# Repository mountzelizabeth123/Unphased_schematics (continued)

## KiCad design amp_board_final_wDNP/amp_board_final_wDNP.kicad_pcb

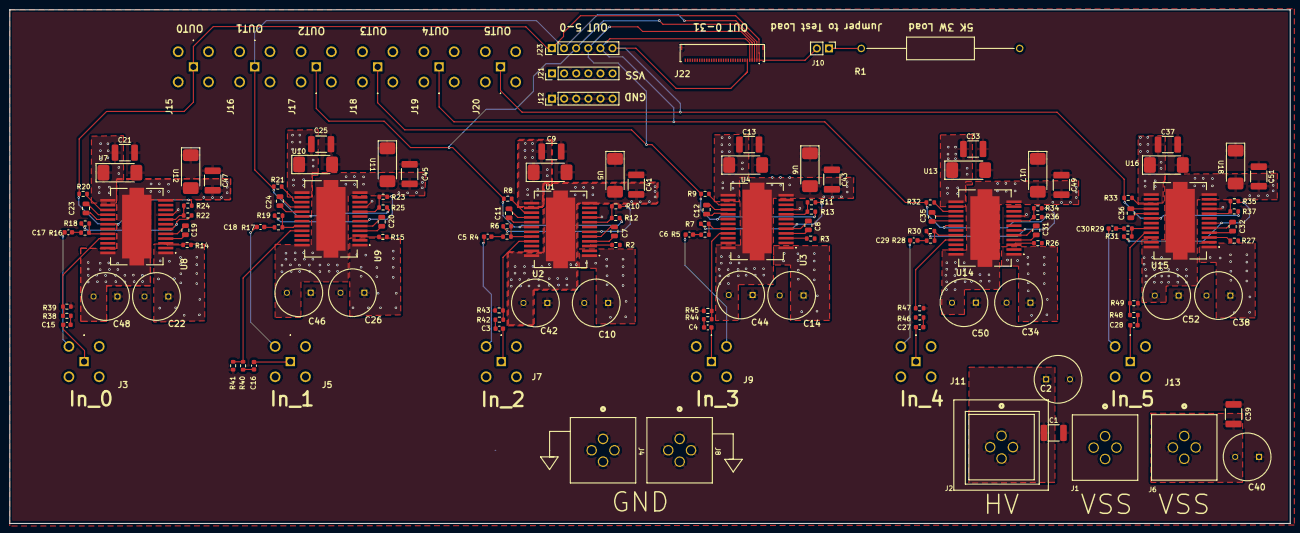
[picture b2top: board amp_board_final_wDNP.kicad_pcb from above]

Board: 4 copper layers, 268.3 x 107.7 mm, 141 parts (0 on the bottom side), 94 nets.

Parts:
C1, C9, C13, C21, C25, C33, C37, C39, C41, C43, C45, C47, C49, C51: 0.1u, 500V; C_1812_4532Metric
C2, C10, C14, C22, C26, C34, C38, C40, C42, C44, C46, C48, C50, C52: EEU-EB2G100
C3, C4, C5, C6, C15, C16, C17, C18, C27, C28, C29, C30: 0.1u, 10V; C_0603_1608Metric
C7, C8, C19, C20, C31, C32: 0.75pF, 250V; C_0805_2012Metric
C11, C12, C23, C24, C35, C36: 0.2pF, 250V; C_0805_2012Metric
J1, J4, J6, J8: CT3151V1-0; banana_plug_CT3151V1-0
J2: CT3151V1-2; banana_plug_CT3151V1-0
J3, J5, J7, J9, J11, J13, J15, J16, J17, J18, J19, J20: SMA_RF2-04A-T-00-50-G; 112404
J10: Conn_01x02_Pin; PinHeader_1x02_P2.54mm_Vertical
J12, J21, J23: Conn_01x06_Pin; PinHeader_1x06_P2.54mm_Vertical
J22: 503480-3200; Molex_5034803200
R1: 5k, 3W; RESAD3322W86L1422D475
R2, R3, R8, R9, R14, R15, R20, R21, R26, R27, R32, R33: 22.6; R_0603_1608Metric
R4, R5, R10, R11, R16, R17, R22, R23, R28, R29, R34, R35, R38, R40, R42, R44, R46, R48: 10; R_0603_1608Metric
R6, R7, R12, R13, R18, R19, R24, R25, R30, R31, R36, R37: 70.7; R_0603_1608Metric
R39, R41, R43, R45, R47, R49: 100; R_0603_1608Metric
U1, U4, U5, U6, U7, U10, U11, U12, U13, U16, U17, U18: SMCJ150A; SMCJ150A-13-F
U2, U3, U8, U9, U14, U15: PA343; PA341DF

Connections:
/amp_0/input_0a_lv: R38.1, R39.2, U8.21 (+IN_A)
/amp_0/input_0b_lv: C17.2, R16.2
/amp_0/input_1a_lv: R40.1, R41.2, U9.21 (+IN_A)
/amp_0/input_1b_lv: C18.2, R17.2
/amp_0/output0_mv: R18.1, R22.2, U8.6 (OUT_A)
/amp_0/output1_mv: R19.1, R23.2, U9.6 (OUT_A)
/amp_1/input_2a_lv: R42.1, R43.2, U2.21 (+IN_A)
/amp_1/input_2b_lv: C5.2, R4.2
/amp_1/input_3a_lv: R44.1, R45.2, U3.21 (+IN_A)
/amp_1/input_3b_lv: C6.2, R5.2
/amp_1/output2_mv: R6.1, R10.2, U2.6 (OUT_A)
/amp_1/output3_mv: R7.1, R11.2, U3.6 (OUT_A)
/amp_2/input_4a_lv: R46.1, R47.2, U14.21 (+IN_A)
/amp_2/input_4b_lv: C29.2, R28.2
/amp_2/input_5a_lv: R48.1, R49.2, U15.21 (+IN_A)
/amp_2/input_5b_lv: C30.2, R29.2
/amp_2/output4_mv: R30.1, R34.2, U14.6 (OUT_A)
/amp_2/output5_mv: R31.1, R35.2, U15.6 (OUT_A)
GND: C1.2, C2.2 (-), C9.2, C10.2 (-), C13.2, C14.2 (-), C21.2, C22.2 (-), C25.2, C26.2 (-), C33.2, C34.2 (-), C37.2, C38.2 (-), C39.2, C40.1 (+), C41.1, C42.1 (+), C43.1, C44.1 (+), C45.1, C46.1 (+), C47.1, C48.1 (+), C49.1, C50.1 (+), C51.1, C52.1 (+), J4.1, J4.2, J4.3, J4.4, J8.1, J8.2, J8.3, J8.4, J12.1, J12.2, J12.3, J12.4, J12.5, J12.6, J22.33, J22.34, R39.1, R41.1, R43.1, R45.1, R47.1, R49.1, U1.2 (A), U2.9 (+IN_B), U3.9 (+IN_B), U4.2 (A), U5.1 (K), U6.1 (K), U7.2 (A), U8.9 (+IN_B), U9.9 (+IN_B), U10.2 (A), U11.1 (K), U12.1 (K), U13.2 (A), U14.9 (+IN_B), U15.9 (+IN_B), U16.2 (A), U17.1 (K), U18.1 (K)
HV: C1.1, C2.1 (+), C9.1, C10.1 (+), C13.1, C14.1 (+), C21.1, C22.1 (+), C25.1, C26.1 (+), C33.1, C34.1 (+), C37.1, C38.1 (+), J2.1, J2.2, J2.3, J2.4, U1.1 (K), U2.1, U2.13, U3.1, U3.13, U4.1 (K), U7.1 (K), U8.1, U8.13, U9.1, U9.13, U10.1 (K), U13.1 (K), U14.1, U14.13, U15.1, U15.13, U16.1 (K)
unnamed: C3.2, R42.2
unnamed: C4.2, R44.2
unnamed: C15.2, R38.2
unnamed: C16.2, R40.2
unnamed: C27.2, R46.2
unnamed: C28.2, R48.2
unnamed: J10.1, R1.1
unnamed: R4.1, R6.2, U2.20 (-IN_A)
unnamed: C7.1, U2.4 (CC_A_1)
unnamed: C7.2, U2.5 (CC_A_2)
unnamed: R2.1, U2.3 (CL_A)
unnamed: R10.1, R12.2, U2.8 (-IN_B)
unnamed: C11.1, U2.16 (CC_B_1)
unnamed: C11.2, U2.17 (CC_B_2)
unnamed: R8.1, U2.15 (CL_B)
unnamed: R5.1, R7.2, U3.20 (-IN_A)
unnamed: C8.1, U3.4 (CC_A_1)
unnamed: C8.2, U3.5 (CC_A_2)
unnamed: R3.1, U3.3 (CL_A)
unnamed: R11.1, R13.2, U3.8 (-IN_B)
unnamed: C12.1, U3.16 (CC_B_1)
unnamed: C12.2, U3.17 (CC_B_2)
unnamed: R9.1, U3.15 (CL_B)
unnamed: R16.1, R18.2, U8.20 (-IN_A)
unnamed: C19.1, U8.4 (CC_A_1)
unnamed: C19.2, U8.5 (CC_A_2)
unnamed: R14.1, U8.3 (CL_A)
unnamed: R22.1, R24.2, U8.8 (-IN_B)
unnamed: C23.1, U8.16 (CC_B_1)
unnamed: C23.2, U8.17 (CC_B_2)
unnamed: R20.1, U8.15 (CL_B)
unnamed: R17.1, R19.2, U9.20 (-IN_A)
unnamed: C20.1, U9.4 (CC_A_1)
unnamed: C20.2, U9.5 (CC_A_2)
unnamed: R15.1, U9.3 (CL_A)
unnamed: R23.1, R25.2, U9.8 (-IN_B)
unnamed: C24.1, U9.16 (CC_B_1)
unnamed: C24.2, U9.17 (CC_B_2)
unnamed: R21.1, U9.15 (CL_B)
unnamed: R28.1, R30.2, U14.20 (-IN_A)
unnamed: C31.1, U14.4 (CC_A_1)
unnamed: C31.2, U14.5 (CC_A_2)
unnamed: R26.1, U14.3 (CL_A)
unnamed: R34.1, R36.2, U14.8 (-IN_B)
unnamed: C35.1, U14.16 (CC_B_1)
unnamed: C35.2, U14.17 (CC_B_2)
unnamed: R32.1, U14.15 (CL_B)
unnamed: R29.1, R31.2, U15.20 (-IN_A)
unnamed: C32.1, U15.4 (CC_A_1)
unnamed: C32.2, U15.5 (CC_A_2)
unnamed: R27.1, U15.3 (CL_A)
unnamed: R35.1, R37.2, U15.8 (-IN_B)
unnamed: C36.1, U15.16 (CC_B_1)
unnamed: C36.2, U15.17 (CC_B_2)
unnamed: R33.1, U15.15 (CL_B)
VSS: C39.1, C40.2 (-), C41.2, C42.2 (-), C43.2, C44.2 (-), C45.2, C46.2 (-), C47.2, C48.2 (-), C49.2, C50.2 (-), C51.2, C52.2 (-), J1.1, J1.2, J1.3, J1.4, J6.1, J6.2, J6.3, J6.4, J15.2, J15.3 (Ext), J15.4 (Ext), J15.5 (Ext), J16.2, J16.3 (Ext), J16.4 (Ext), J16.5 (Ext), J17.2, J17.3 (Ext), J17.4 (Ext), J17.5 (Ext), J18.2, J18.3 (Ext), J18.4 (Ext), J18.5 (Ext), J19.2, J19.3 (Ext), J19.4 (Ext), J19.5 (Ext), J20.2, J20.3 (Ext), J20.4 (Ext), J20.5 (Ext), J21.1, J21.2, J21.3, J21.4, J21.5, J21.6, R1.2, U2.12, U2.24, U2.25 (EPAD), U2.26, U2.27, U3.12, U3.24, U3.25 (EPAD), U3.26, U3.27, U5.2 (A), U6.2 (A), U8.12, U8.24, U8.25 (EPAD), U8.26, U8.27, U9.12, U9.24, U9.25 (EPAD), U9.26, U9.27, U11.2 (A), U12.2 (A), U14.12, U14.24, U14.25 (EPAD), U14.26, U14.27, U15.12, U15.24, U15.25 (EPAD), U15.26, U15.27, U17.2 (A), U18.2 (A)
input_0a: C15.1, J3.1
input_0b: C17.1, J3.2, J3.3 (Ext), J3.4 (Ext), J3.5 (Ext)
input_1a: C16.1, J5.1
input_1b: C18.1, J5.2, J5.3 (Ext), J5.4 (Ext), J5.5 (Ext)
input_2a: C3.1, J7.1
input_2b: C5.1, J7.2, J7.3 (Ext), J7.4 (Ext), J7.5 (Ext)
input_3a: C4.1, J9.1
input_3b: C6.1, J9.2, J9.3 (Ext), J9.4 (Ext), J9.5 (Ext)
input_4a: C27.1, J11.1
input_4b: C29.1, J11.2, J11.3 (Ext), J11.4 (Ext), J11.5 (Ext)
input_5a: C28.1, J13.1
input_5b: C30.1, J13.2, J13.3 (Ext), J13.4 (Ext), J13.5 (Ext)
output_0: J10.2, J15.1, J22.1, J23.1, R20.2, R24.1, U8.18 (OUT_B)
output_1: J16.1, J22.2, J23.2, R21.2, R25.1, U9.18 (OUT_B)
output_2: J17.1, J22.3, J23.3, R8.2, R12.1, U2.18 (OUT_B)
output_3: J18.1, J22.4, J23.4, R9.2, R13.1, U3.18 (OUT_B)
output_4: J19.1, J22.5, J23.5, R32.2, R36.1, U14.18 (OUT_B)
output_5: J20.1, J22.6, J23.6, R33.2, R37.1, U15.18 (OUT_B)

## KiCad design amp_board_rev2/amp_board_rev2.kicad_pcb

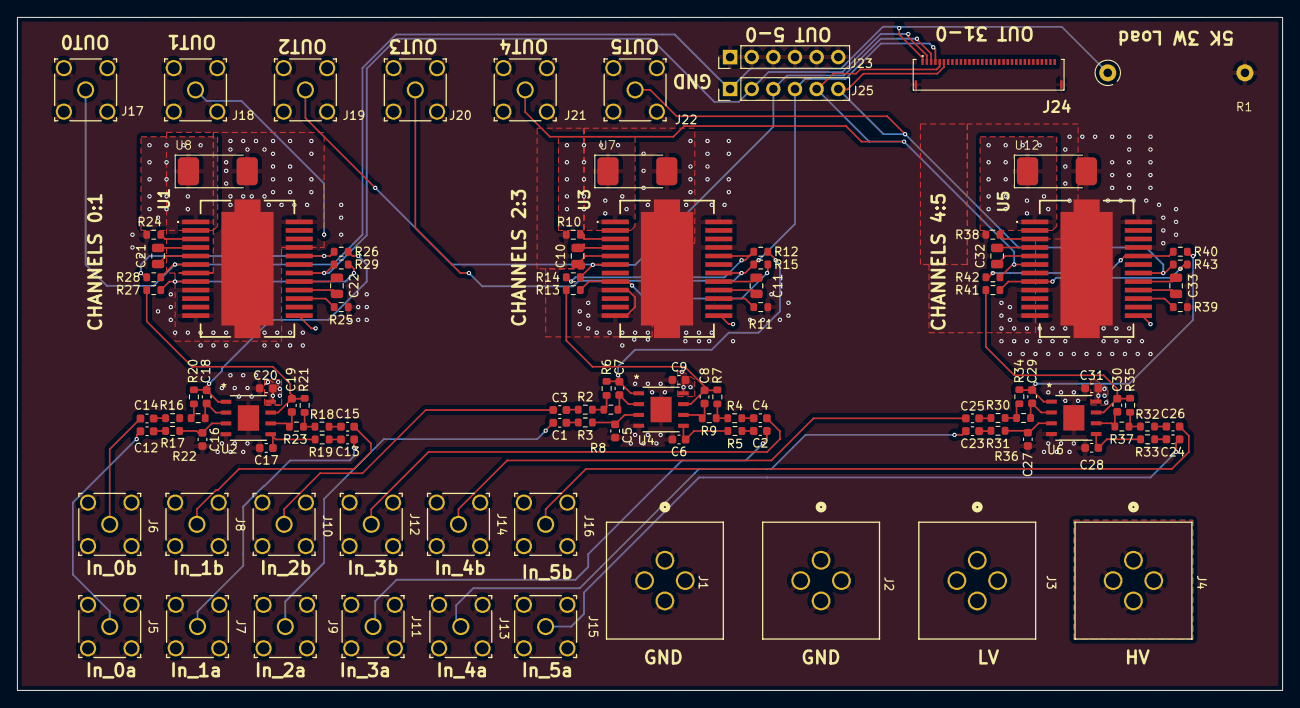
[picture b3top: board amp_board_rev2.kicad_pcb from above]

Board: 4 copper layers, 148.5 x 79.0 mm, 110 parts (0 on the bottom side), 84 nets.

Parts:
C1, C2, C3, C4, C9, C12, C13, C14, C15, C20, C23, C24, C25, C26, C31: 0.1u; C_0603_1608Metric
C5, C6, C16, C17, C27, C28: 1.56pF; C_0603_1608Metric
C7, C8, C18, C19, C29, C30: 1pF; C_0603_1608Metric
C10, C11, C21, C22, C32, C33: 0.75pF, 500V; C_0805_2012Metric
J1, J2: CT3151V1-0; banana_plug_CT3151V1-0
J3, J4: CT3151V1-2; banana_plug_CT3151V1-0
J5, J6, J7, J8, J9, J10, J11, J12, J13, J14, J15, J16, J17, J18, J19, J20, J21, J22: SMA_RF2-04A-T-00-50-G; CONN_RF2-04A-T-00-50-G_ADM
J23, J25: Conn_01x06_Pin; PinHeader_1x06_P2.54mm_Vertical
J24: 503480-3200; Molex_5034803200
R1: R_US; RS02B5K000FB12
R2, R4, R16, R18, R30, R32: 1k; R_0603_1608Metric
R3, R5, R8, R9, R17, R19, R22, R23, R31, R33, R36, R37: R_US; R_0603_1608Metric
R6, R7, R20, R21, R34, R35: 4k; R_0603_1608Metric
R10, R11, R24, R25, R38, R39: 22.6; R_0603_1608Metric
R12, R13, R26, R27, R40, R41: 1R; R_0603_1608Metric
R14, R15, R28, R29, R42, R43: 25R; R_0603_1608Metric
U1, U3, U5: PA341DF
U2, U4, U6: OPA2211AIDDAR_L
U7, U8, U12: SMCJ150A-13-F

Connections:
+12V: C9.1, C20.1, C31.1, J3.1, J3.2, J3.3, J3.4, U2.8, U4.8, U6.8
/amp_0/output0_lv: C18.1, R20.1, R26.2, U2.1 (OUTA)
/amp_0/output1_lv: C19.1, R21.1, R27.2, U2.7 (OUTB)
/amp_1/output2_lv: C7.1, R6.1, R12.2, U4.1 (OUTA)
/amp_1/output3_lv: C8.1, R7.1, R13.2, U4.7 (OUTB)
/amp_2/output4_lv: C29.1, R34.1, R40.2, U6.1 (OUTA)
/amp_2/output5_lv: C30.1, R35.1, R41.2, U6.7 (OUTB)
GND: C5.2, C6.2, C9.2, C16.2, C17.2, C20.2, C27.2, C28.2, C31.2, J1.1, J1.2, J1.3, J1.4, J2.1, J2.2, J2.3, J2.4, J5.2, J5.3 (Ext), J5.4 (Ext), J5.5 (Ext), J6.2, J6.3 (Ext), J6.4 (Ext), J6.5 (Ext), J7.2, J7.3 (Ext), J7.4 (Ext), J7.5 (Ext), J8.2, J8.3 (Ext), J8.4 (Ext), J8.5 (Ext), J9.2, J9.3 (Ext), J9.4 (Ext), J9.5 (Ext), J10.2, J10.3 (Ext), J10.4 (Ext), J10.5 (Ext), J11.2, J11.3 (Ext), J11.4 (Ext), J11.5 (Ext), J12.2, J12.3 (Ext), J12.4 (Ext), J12.5 (Ext), J13.2, J13.3 (Ext), J13.4 (Ext), J13.5 (Ext), J14.2, J14.3 (Ext), J14.4 (Ext), J14.5 (Ext), J15.2, J15.3 (Ext), J15.4 (Ext), J15.5 (Ext), J16.2, J16.3 (Ext), J16.4 (Ext), J16.5 (Ext), J17.2, J17.3 (Ext), J17.4 (Ext), J17.5 (Ext), J18.2, J18.3 (Ext), J18.4 (Ext), J18.5 (Ext), J19.2, J19.3 (Ext), J19.4 (Ext), J19.5 (Ext), J20.2, J20.3 (Ext), J20.4 (Ext), J20.5 (Ext), J21.2, J21.3 (Ext), J21.4 (Ext), J21.5 (Ext), J22.2, J22.3 (Ext), J22.4 (Ext), J22.5 (Ext), J23.1, J23.2, J23.3, J23.4, J23.5, J23.6, J24.33, J24.34, R1.2, R10.2, R11.2, R24.2, R25.2, R38.2, R39.2, U1.9 (+IN_B), U1.12, U1.21 (+IN_A), U1.24, U1.25 (EPAD), U1.26, U1.27, U2.4, U2.EPAD, U3.9 (+IN_B), U3.12, U3.21 (+IN_A), U3.24, U3.25 (EPAD), U3.26, U3.27, U4.4, U4.EPAD, U5.9 (+IN_B), U5.12, U5.21 (+IN_A), U5.24, U5.25 (EPAD), U5.26, U5.27, U6.4, U6.EPAD, U7.2 (A), U8.2 (A), U12.2 (A)
HV: J4.1, J4.2, J4.3, J4.4, U1.1, U1.13, U3.1, U3.13, U5.1, U5.13, U7.1 (K), U8.1 (K), U12.1 (K)
unnamed: C1.2, R3.2
unnamed: C2.2, R5.2
unnamed: C3.2, R2.2
unnamed: C4.2, R4.2
unnamed: C12.2, R17.2
unnamed: C13.2, R19.2
unnamed: C14.2, R16.2
unnamed: C15.2, R18.2
unnamed: C23.2, R31.2
unnamed: C24.2, R33.2
unnamed: C25.2, R30.2
unnamed: C26.2, R32.2
unnamed: R2.1, R6.2, R8.2
unnamed: R4.1, R7.2, R9.2
unnamed: R16.1, R20.2, R22.2
unnamed: R18.1, R21.2, R23.2
unnamed: R30.1, R34.2, R36.2
unnamed: R32.1, R35.2, R37.2
unnamed: R26.1, R28.2, U1.20 (-IN_A)
unnamed: C21.1, U1.4 (CC_A_1)
unnamed: C21.2, U1.5 (CC_A_2)
unnamed: R24.1, U1.3 (CL_A)
unnamed: U1.2 (NC_1), U1.7 (NC_2), U1.10 (NC_3), U1.11 (NC_4), U1.14 (NC_5), U1.19 (NC_6), U1.22 (NC_7), U1.23 (NC_8)
unnamed: R27.1, R29.2, U1.8 (-IN_B)
unnamed: C22.1, U1.16 (CC_B_1)
unnamed: C22.2, U1.17 (CC_B_2)
unnamed: R25.1, U1.15 (CL_B)
unnamed: C16.1, R17.1, U2.3 (INA+)
unnamed: C18.2, R22.1, U2.2 (INA-)
unnamed: C17.1, R19.1, U2.5 (INB+)
unnamed: C19.2, R23.1, U2.6 (INB-)
unnamed: R12.1, R14.2, U3.20 (-IN_A)
unnamed: C10.1, U3.4 (CC_A_1)
unnamed: C10.2, U3.5 (CC_A_2)
unnamed: R10.1, U3.3 (CL_A)
unnamed: U3.2 (NC_1), U3.7 (NC_2), U3.10 (NC_3), U3.11 (NC_4), U3.14 (NC_5), U3.19 (NC_6), U3.22 (NC_7), U3.23 (NC_8)
unnamed: R13.1, R15.2, U3.8 (-IN_B)
unnamed: C11.1, U3.16 (CC_B_1)
unnamed: C11.2, U3.17 (CC_B_2)
unnamed: R11.1, U3.15 (CL_B)
unnamed: C5.1, R3.1, U4.3 (INA+)
unnamed: C7.2, R8.1, U4.2 (INA-)
unnamed: C6.1, R5.1, U4.5 (INB+)
unnamed: C8.2, R9.1, U4.6 (INB-)
unnamed: R40.1, R42.2, U5.20 (-IN_A)
unnamed: C32.1, U5.4 (CC_A_1)
unnamed: C32.2, U5.5 (CC_A_2)
unnamed: R38.1, U5.3 (CL_A)
unnamed: U5.2 (NC_1), U5.7 (NC_2), U5.10 (NC_3), U5.11 (NC_4), U5.14 (NC_5), U5.19 (NC_6), U5.22 (NC_7), U5.23 (NC_8)
unnamed: R41.1, R43.2, U5.8 (-IN_B)
unnamed: C33.1, U5.16 (CC_B_1)
unnamed: C33.2, U5.17 (CC_B_2)
unnamed: R39.1, U5.15 (CL_B)
unnamed: C27.1, R31.1, U6.3 (INA+)
unnamed: C29.2, R36.1, U6.2 (INA-)
unnamed: C28.1, R33.1, U6.5 (INB+)
unnamed: C30.2, R37.1, U6.6 (INB-)
input_0a: C12.1, J5.1
input_0b: C14.1, J6.1
input_1a: C13.1, J7.1
input_1b: C15.1, J8.1
input_2a: C1.1, J9.1
input_2b: C3.1, J10.1
input_3a: C2.1, J11.1
input_3b: C4.1, J12.1
input_4a: C23.1, J13.1
input_4b: C25.1, J14.1
input_5a: C24.1, J15.1
input_5b: C26.1, J16.1
output_0: J17.1, J24.1, J25.1, R1.1, R28.1, U1.6 (OUT_A)
output_1: J18.1, J24.2, J25.2, R29.1, U1.18 (OUT_B)
output_2: J19.1, J24.3, J25.3, R14.1, U3.6 (OUT_A)
output_3: J20.1, J24.4, J25.4, R15.1, U3.18 (OUT_B)
output_4: J21.1, J24.5, J25.5, R42.1, U5.6 (OUT_A)
output_5: J22.1, J24.6, J25.6, R43.1, U5.18 (OUT_B)

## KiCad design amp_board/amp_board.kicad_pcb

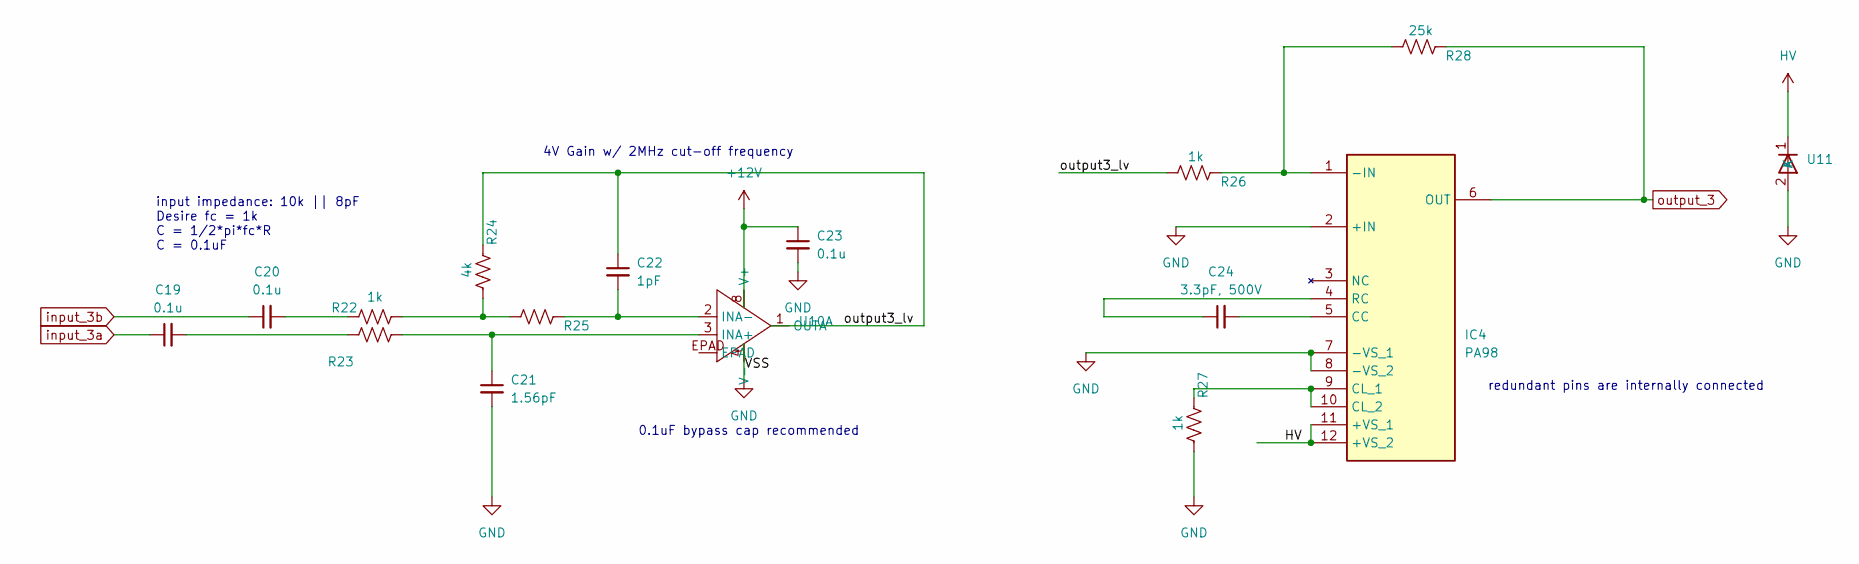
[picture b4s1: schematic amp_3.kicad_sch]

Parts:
C19, C20, C23: 0.1u; C_0603_1608Metric
C21: 1.56pF; C_0603_1608Metric
C22: 1pF; C_0603_1608Metric
C24: 3.3pF, 500V; C_0805_2012Metric
IC4: PA98; Mouser Part Number 137-PA98
R22, R26, R27: 1k; R_0603_1608Metric
R23, R25: R_US; R_0603_1608Metric
R24: 4k; R_0603_1608Metric
R28: 25k; R_0603_1608Metric
U10: OPA2211AIDDAR_L
U11: SMCJ150A-13-F

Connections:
+12V: C23.1, U10.8 (V+); also elsewhere on the board
/amp_3/output3_lv: C22.1, R24.1, R26.2, U10.1 (OUTA)
GND: C21.2, C23.2, IC4.2 (+IN), IC4.7 (-VS_1), IC4.8 (-VS_2), R27.2, U10.4 (V-), U11.2 (A); also elsewhere on the board
HV: IC4.11 (+VS_1), IC4.12 (+VS_2), U11.1 (K); also elsewhere on the board
unnamed: C19.2, R23.2
unnamed: C20.2, R22.2
unnamed: IC4.1 (-IN), R26.1, R28.2
unnamed: C24.2, IC4.5 (CC)
unnamed: IC4.9 (CL_1), IC4.10 (CL_2), R27.1
unnamed: C24.1, IC4.4 (RC)
unnamed: R22.1, R24.2, R25.2
unnamed: C21.1, R23.1, U10.3 (INA+)
unnamed: C22.2, R25.1, U10.2 (INA-)
input_3a: C19.1; also elsewhere on the board
input_3b: C20.1; also elsewhere on the board
output_3: IC4.6 (OUT), R28.1; also elsewhere on the board

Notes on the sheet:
input impedance: 10k || 8pF Desire fc = 1k C = 1/2*pi*fc*R C = 0.1uF
0.1uF bypass cap recommended
4V Gain w/ 2MHz cut-off frequency
redundant pins are internally connected

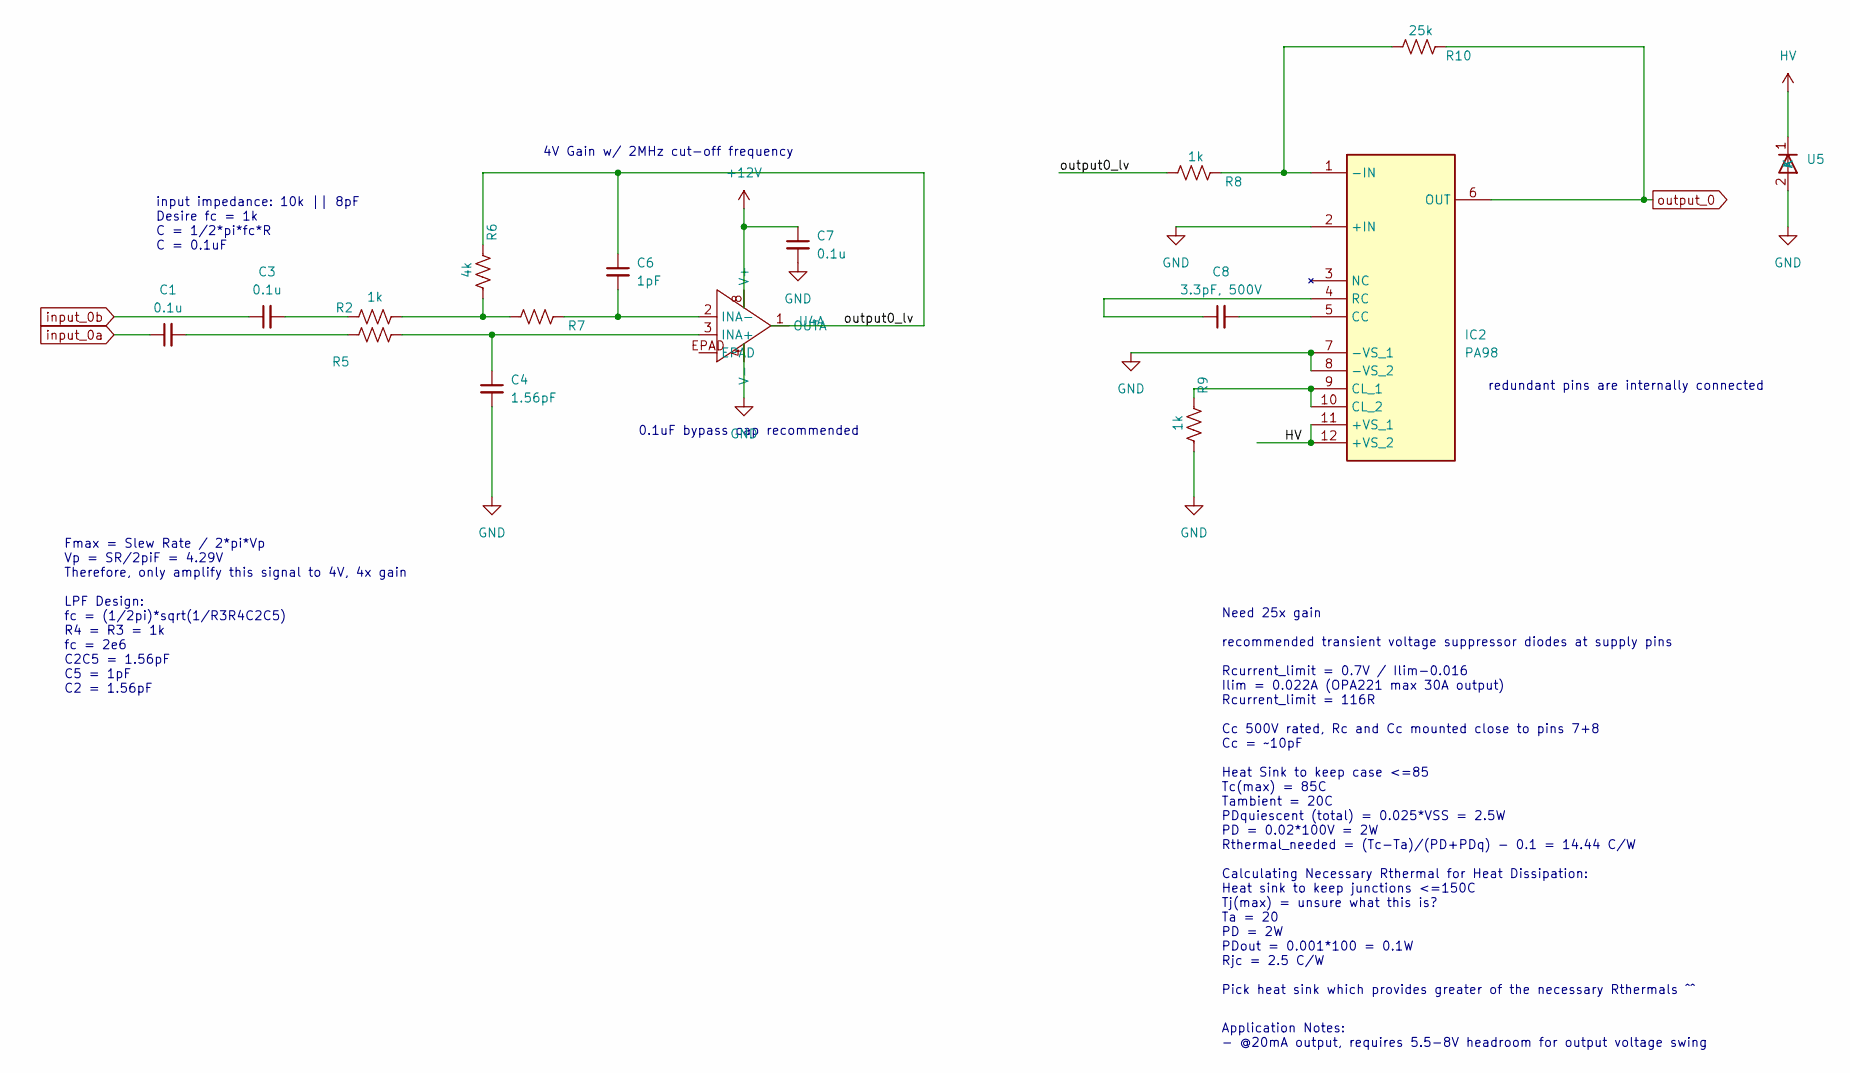
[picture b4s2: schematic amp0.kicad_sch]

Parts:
C1, C3, C7: 0.1u; C_0603_1608Metric
C4: 1.56pF; C_0603_1608Metric
C6: 1pF; C_0603_1608Metric
C8: 3.3pF, 500V; C_0805_2012Metric
IC2: PA98; Mouser Part Number 137-PA98
R2, R8, R9: 1k; R_0603_1608Metric
R5, R7: R_US; R_0603_1608Metric
R6: 4k; R_0603_1608Metric
R10: 25k; R_0603_1608Metric
U4: OPA2211AIDDAR_L
U5: SMCJ150A-13-F

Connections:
+12V: C7.1, U4.8 (V+); also elsewhere on the board
/amp_0/output0_lv: C6.1, R6.1, R8.2, U4.1 (OUTA)
GND: C4.2, C7.2, IC2.2 (+IN), IC2.7 (-VS_1), IC2.8 (-VS_2), R9.2, U4.4 (V-), U5.2 (A); also elsewhere on the board
HV: IC2.11 (+VS_1), IC2.12 (+VS_2), U5.1 (K); also elsewhere on the board
unnamed: C1.2, R5.2
unnamed: C3.2, R2.2
unnamed: IC2.1 (-IN), R8.1, R10.2
unnamed: C8.2, IC2.5 (CC)
unnamed: IC2.9 (CL_1), IC2.10 (CL_2), R9.1
unnamed: C8.1, IC2.4 (RC)
unnamed: R2.1, R6.2, R7.2
unnamed: C4.1, R5.1, U4.3 (INA+)
unnamed: C6.2, R7.1, U4.2 (INA-)
input_0a: C1.1; also elsewhere on the board
input_0b: C3.1; also elsewhere on the board
output_0: IC2.6 (OUT), R10.1; also elsewhere on the board

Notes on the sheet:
input impedance: 10k || 8pF Desire fc = 1k C = 1/2*pi*fc*R C = 0.1uF
redundant pins are internally connected
4V Gain w/ 2MHz cut-off frequency
Fmax = Slew Rate / 2*pi*Vp Vp = SR/2piF = 4.29V Therefore, only amplify this signal to 4V, 4x gain LPF Design: fc = (1/2pi)*sqrt(1/R3R4C2C5) R4 = R3 = 1k fc = 2e6 C2C5 = 1.56pF C5 = 1pF C2 = 1.56pF
0.1uF bypass cap recommended
Need 25x gain recommended transient voltage suppressor diodes at supply pins Rcurrent_limit = 0.7V / Ilim-0.016 Ilim = 0.022A (OPA221 max 30A output) Rcurrent_limit = 116R Cc 500V rated, Rc and Cc mounted close to pins 7+8 Cc = ~10pF Heat Sink to keep case <=85 Tc(max) = 85C Tambient = 20C PDquiesc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
Application Notes: - @20mA output, requires 5.5-8V headroom for output voltage swing

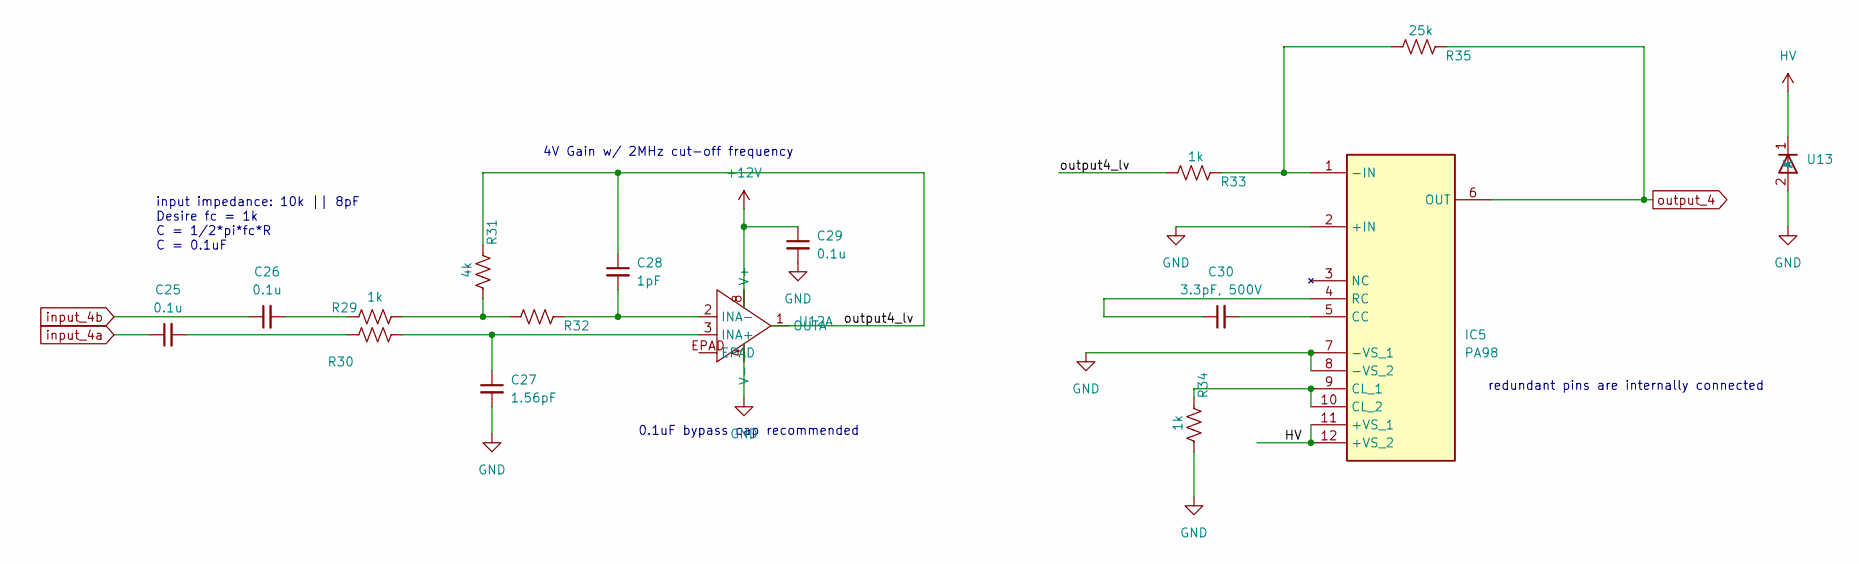
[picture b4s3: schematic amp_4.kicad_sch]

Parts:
C25, C26, C29: 0.1u; C_0603_1608Metric
C27: 1.56pF; C_0603_1608Metric
C28: 1pF; C_0603_1608Metric
C30: 3.3pF, 500V; C_0805_2012Metric
IC5: PA98; Mouser Part Number 137-PA98
R29, R33, R34: 1k; R_0603_1608Metric
R30, R32: R_US; R_0603_1608Metric
R31: 4k; R_0603_1608Metric
R35: 25k; R_0603_1608Metric
U12: OPA2211AIDDAR_L
U13: SMCJ150A-13-F

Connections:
+12V: C29.1, U12.8 (V+); also elsewhere on the board
/amp_4/output4_lv: C28.1, R31.1, R33.2, U12.1 (OUTA)
GND: C27.2, C29.2, IC5.2 (+IN), IC5.7 (-VS_1), IC5.8 (-VS_2), R34.2, U12.4 (V-), U13.2 (A); also elsewhere on the board
HV: IC5.11 (+VS_1), IC5.12 (+VS_2), U13.1 (K); also elsewhere on the board
unnamed: C25.2, R30.2
unnamed: C26.2, R29.2
unnamed: IC5.1 (-IN), R33.1, R35.2
unnamed: C30.2, IC5.5 (CC)
unnamed: IC5.9 (CL_1), IC5.10 (CL_2), R34.1
unnamed: C30.1, IC5.4 (RC)
unnamed: R29.1, R31.2, R32.2
unnamed: C27.1, R30.1, U12.3 (INA+)
unnamed: C28.2, R32.1, U12.2 (INA-)
input_4a: C25.1; also elsewhere on the board
input_4b: C26.1; also elsewhere on the board
output_4: IC5.6 (OUT), R35.1; also elsewhere on the board

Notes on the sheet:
redundant pins are internally connected
0.1uF bypass cap recommended
4V Gain w/ 2MHz cut-off frequency
input impedance: 10k || 8pF Desire fc = 1k C = 1/2*pi*fc*R C = 0.1uF

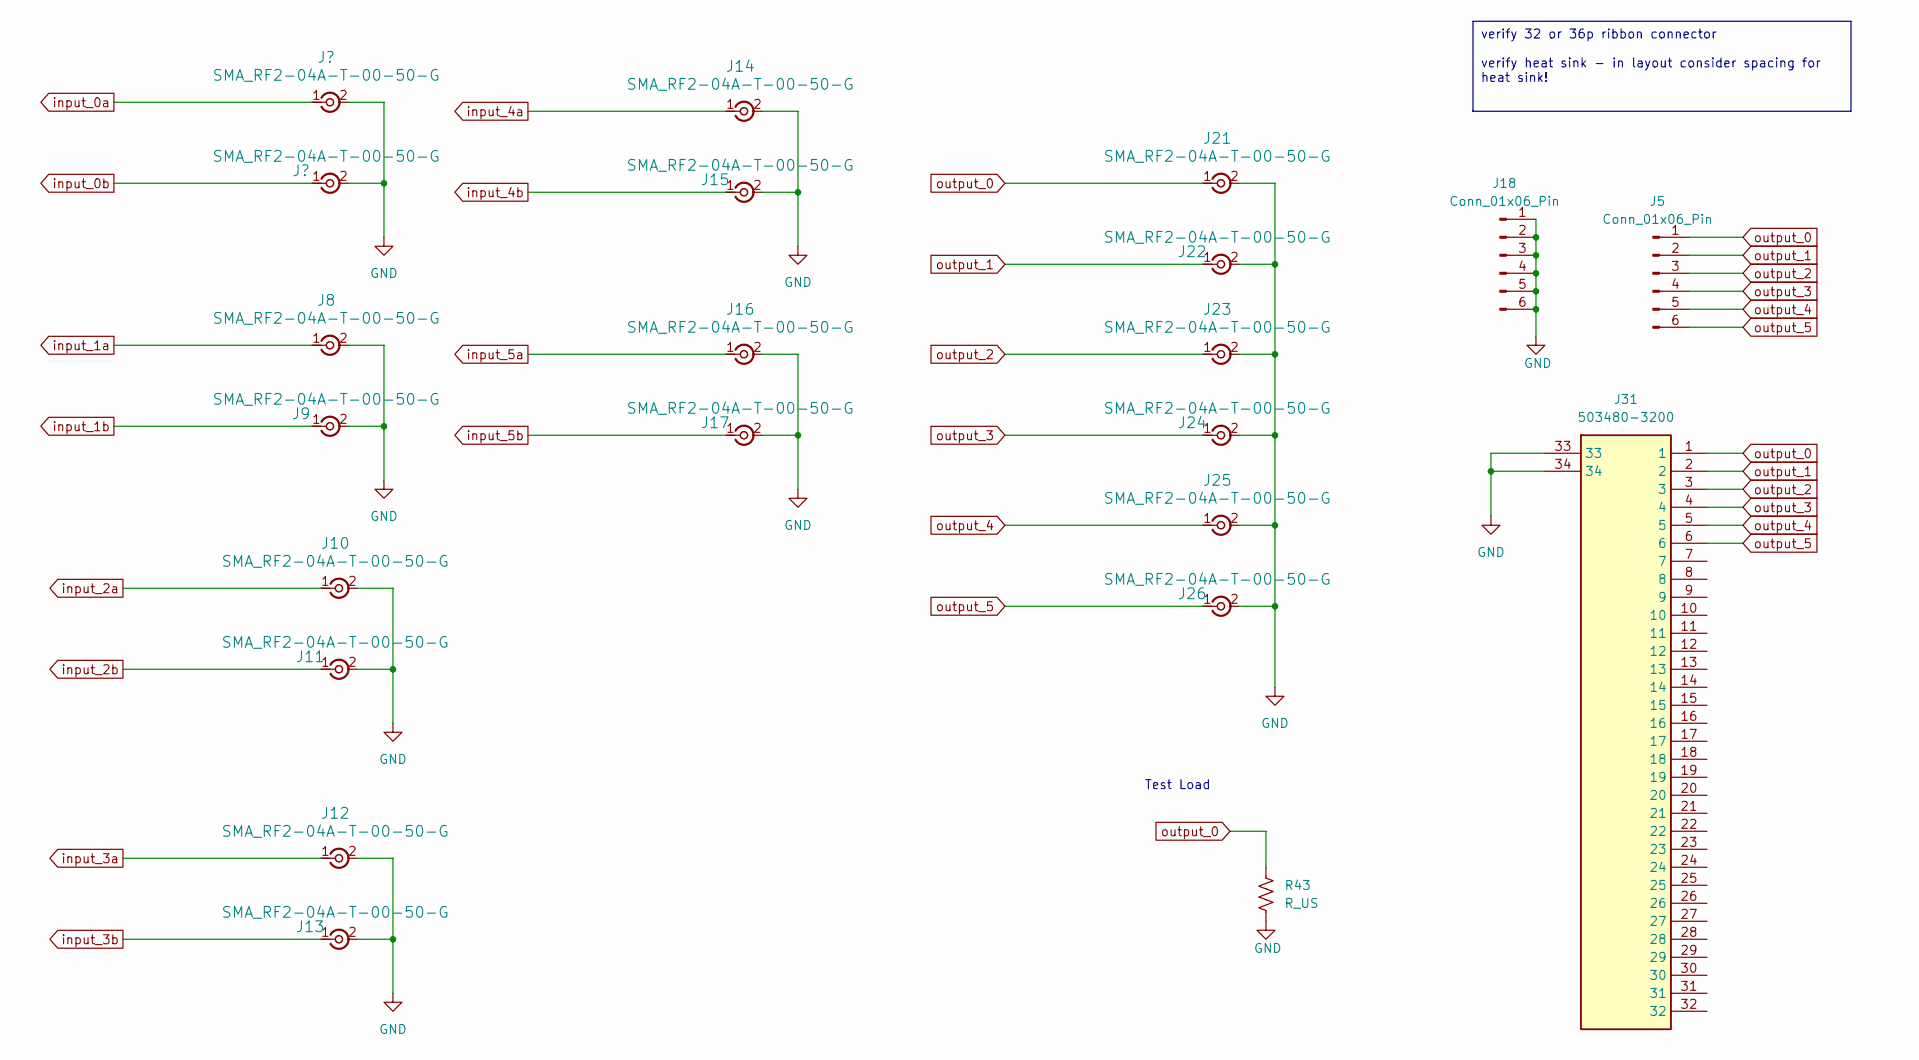
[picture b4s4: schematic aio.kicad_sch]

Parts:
J5, J18: Conn_01x06_Pin; PinHeader_1x06_P1.00mm_Vertical
J8, J9, J10, J11, J12, J13, J14, J15, J16, J17, J21, J22, J23, J24, J25, J26: SMA_RF2-04A-T-00-50-G; CONN_RF2-04A-T-00-50-G_ADM
J31: 503480-3200; Molex_5034803200; Mouser Part Number 538-503480-3200
R43: R_US; RS02B5K000FB12

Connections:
GND: J8.2, J8.3 (Ext), J8.4 (Ext), J8.5 (Ext), J9.2, J9.3 (Ext), J9.4 (Ext), J9.5 (Ext), J10.2, J10.3 (Ext), J10.4 (Ext), J10.5 (Ext), J11.2, J11.3 (Ext), J11.4 (Ext), J11.5 (Ext), J12.2, J12.3 (Ext), J12.4 (Ext), J12.5 (Ext), J13.2, J13.3 (Ext), J13.4 (Ext), J13.5 (Ext), J14.2, J14.3 (Ext), J14.4 (Ext), J14.5 (Ext), J15.2, J15.3 (Ext), J15.4 (Ext), J15.5 (Ext), J16.2, J16.3 (Ext), J16.4 (Ext), J16.5 (Ext), J17.2, J17.3 (Ext), J17.4 (Ext), J17.5 (Ext), J18.1, J18.2, J18.3, J18.4, J18.5, J18.6, J21.2, J21.3 (Ext), J21.4 (Ext), J21.5 (Ext), J22.2, J22.3 (Ext), J22.4 (Ext), J22.5 (Ext), J23.2, J23.3 (Ext), J23.4 (Ext), J23.5 (Ext), J24.2, J24.3 (Ext), J24.4 (Ext), J24.5 (Ext), J25.2, J25.3 (Ext), J25.4 (Ext), J25.5 (Ext), J26.2, J26.3 (Ext), J26.4 (Ext), J26.5 (Ext), J31.33, J31.34, R43.2; also elsewhere on the board
input_1a: J8.1; also elsewhere on the board
input_1b: J9.1; also elsewhere on the board
input_2a: J10.1; also elsewhere on the board
input_2b: J11.1; also elsewhere on the board
input_3a: J12.1; also elsewhere on the board
input_3b: J13.1; also elsewhere on the board
input_4a: J14.1; also elsewhere on the board
input_4b: J15.1; also elsewhere on the board
input_5a: J16.1; also elsewhere on the board
input_5b: J17.1; also elsewhere on the board
output_0: J5.1, J21.1, J31.1, R43.1; also elsewhere on the board
output_1: J5.2, J22.1, J31.2; also elsewhere on the board
output_2: J5.3, J23.1, J31.3; also elsewhere on the board
output_3: J5.4, J24.1, J31.4; also elsewhere on the board
output_4: J5.5, J25.1, J31.5; also elsewhere on the board
output_5: J5.6, J26.1, J31.6; also elsewhere on the board

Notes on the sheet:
verify 32 or 36p ribbon connector verify heat sink - in layout consider spacing for heat sink!
Test Load

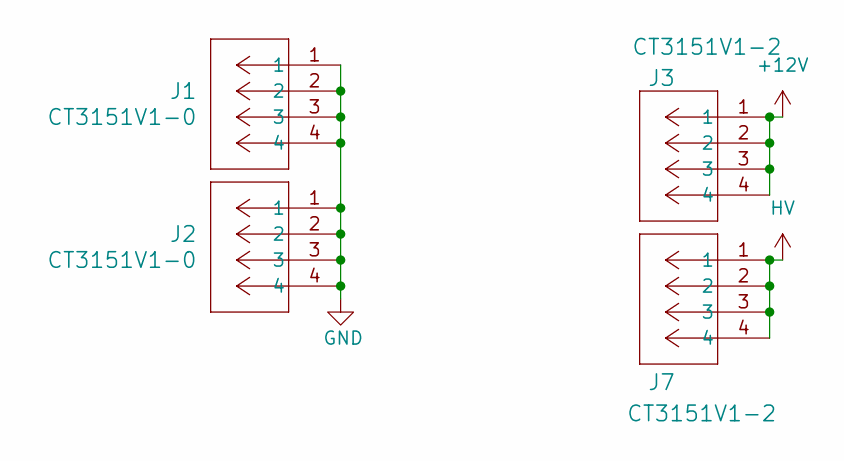
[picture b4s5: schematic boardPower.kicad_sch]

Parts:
J1, J2: CT3151V1-0; banana_plug_CT3151V1-0
J3, J7: CT3151V1-2; banana_plug_CT3151V1-0

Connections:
+12V: J3.1, J3.2, J3.3, J3.4; also elsewhere on the board
GND: J1.1, J1.2, J1.3, J1.4, J2.1, J2.2, J2.3, J2.4; also elsewhere on the board
HV: J7.1, J7.2, J7.3, J7.4; also elsewhere on the board

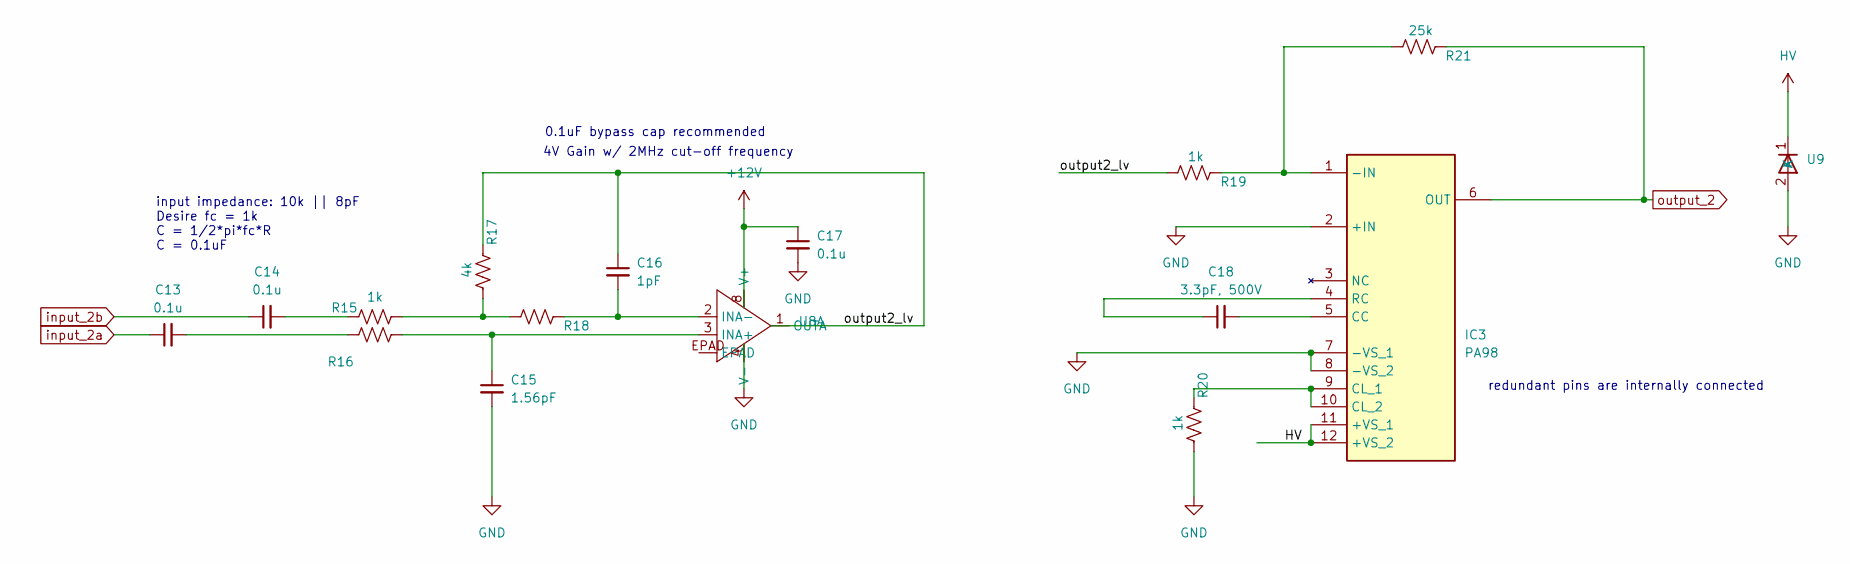
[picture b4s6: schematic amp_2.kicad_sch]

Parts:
C13, C14, C17: 0.1u; C_0603_1608Metric
C15: 1.56pF; C_0603_1608Metric
C16: 1pF; C_0603_1608Metric
C18: 3.3pF, 500V; C_0805_2012Metric
IC3: PA98; Mouser Part Number 137-PA98
R15, R19, R20: 1k; R_0603_1608Metric
R16, R18: R_US; R_0603_1608Metric
R17: 4k; R_0603_1608Metric
R21: 25k; R_0603_1608Metric
U8: OPA2211AIDDAR_L
U9: SMCJ150A-13-F

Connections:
+12V: C17.1, U8.8 (V+); also elsewhere on the board
/amp_2/output2_lv: C16.1, R17.1, R19.2, U8.1 (OUTA)
GND: C15.2, C17.2, IC3.2 (+IN), IC3.7 (-VS_1), IC3.8 (-VS_2), R20.2, U8.4 (V-), U9.2 (A); also elsewhere on the board
HV: IC3.11 (+VS_1), IC3.12 (+VS_2), U9.1 (K); also elsewhere on the board
unnamed: C13.2, R16.2
unnamed: C14.2, R15.2
unnamed: IC3.1 (-IN), R19.1, R21.2
unnamed: C18.2, IC3.5 (CC)
unnamed: IC3.9 (CL_1), IC3.10 (CL_2), R20.1
unnamed: C18.1, IC3.4 (RC)
unnamed: R15.1, R17.2, R18.2
unnamed: C15.1, R16.1, U8.3 (INA+)
unnamed: C16.2, R18.1, U8.2 (INA-)
input_2a: C13.1; also elsewhere on the board
input_2b: C14.1; also elsewhere on the board
output_2: IC3.6 (OUT), R21.1; also elsewhere on the board

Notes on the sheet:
4V Gain w/ 2MHz cut-off frequency
0.1uF bypass cap recommended
redundant pins are internally connected
input impedance: 10k || 8pF Desire fc = 1k C = 1/2*pi*fc*R C = 0.1uF

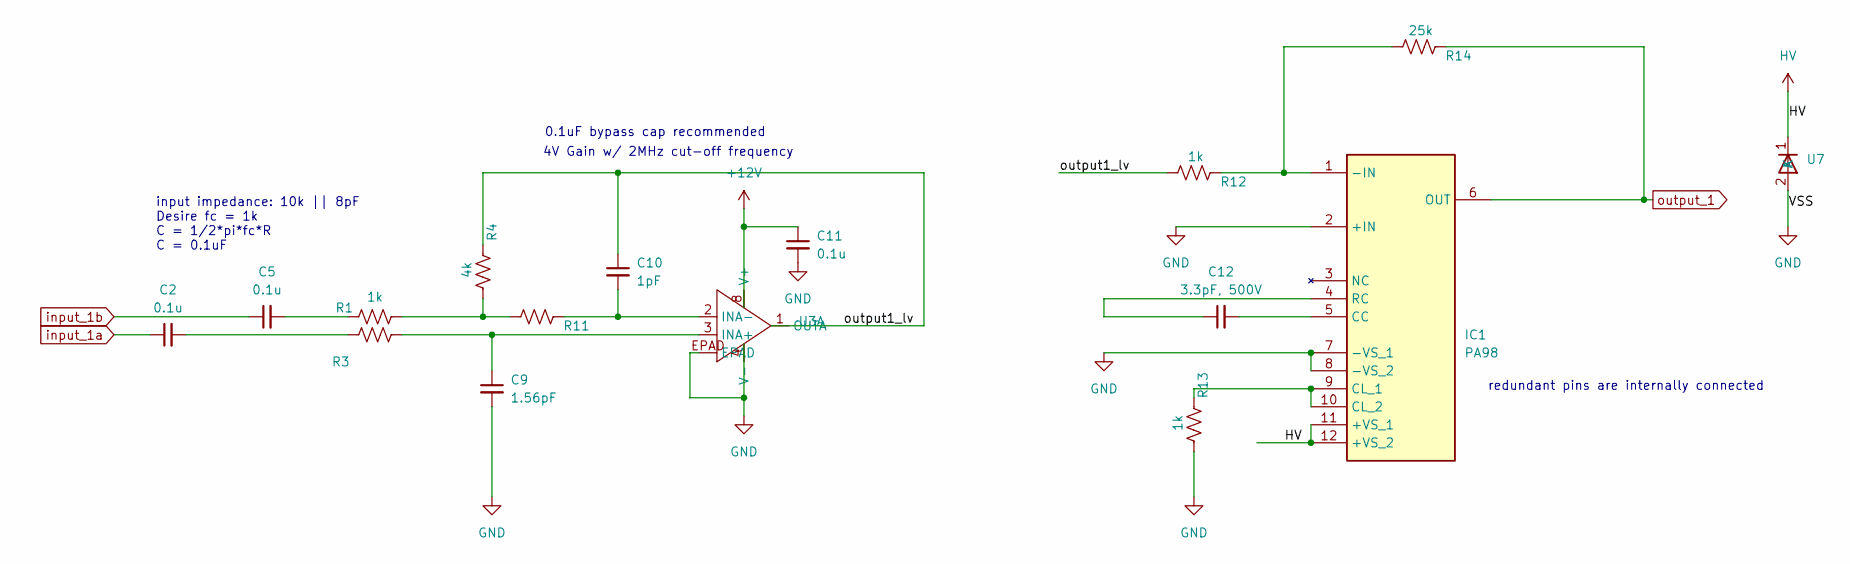
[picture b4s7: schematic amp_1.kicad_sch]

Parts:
C2, C5, C11: 0.1u; C_0603_1608Metric
C9: 1.56pF; C_0603_1608Metric
C10: 1pF; C_0603_1608Metric
C12: 3.3pF, 500V; C_0805_2012Metric
IC1: PA98; Mouser Part Number 137-PA98
R1, R12, R13: 1k; R_0603_1608Metric
R3, R11: R_US; R_0603_1608Metric
R4: 4k; R_0603_1608Metric
R14: 25k; R_0603_1608Metric
U3: OPA2211AIDDAR_L
U7: SMCJ150A-13-F

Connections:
+12V: C11.1, U3.8 (V+); also elsewhere on the board
/amp_1/output1_lv: C10.1, R4.1, R12.2, U3.1 (OUTA)
GND: C9.2, C11.2, IC1.2 (+IN), IC1.7 (-VS_1), IC1.8 (-VS_2), R13.2, U3.4 (V-), U3.EPAD, U7.2 (A); also elsewhere on the board
HV: IC1.11 (+VS_1), IC1.12 (+VS_2), U7.1 (K); also elsewhere on the board
unnamed: C2.2, R3.2
unnamed: C5.2, R1.2
unnamed: IC1.1 (-IN), R12.1, R14.2
unnamed: C12.2, IC1.5 (CC)
unnamed: IC1.9 (CL_1), IC1.10 (CL_2), R13.1
unnamed: C12.1, IC1.4 (RC)
unnamed: R1.1, R4.2, R11.2
unnamed: C9.1, R3.1, U3.3 (INA+)
unnamed: C10.2, R11.1, U3.2 (INA-)
input_1a: C2.1; also elsewhere on the board
input_1b: C5.1; also elsewhere on the board
output_1: IC1.6 (OUT), R14.1; also elsewhere on the board

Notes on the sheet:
input impedance: 10k || 8pF Desire fc = 1k C = 1/2*pi*fc*R C = 0.1uF
redundant pins are internally connected
4V Gain w/ 2MHz cut-off frequency
0.1uF bypass cap recommended
